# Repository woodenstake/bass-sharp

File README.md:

# New take on Thomas Henry's Bass++ but SMD and possibly a few tweaks

## Simulation in KiCad
I can run transient simulation with ngspice in KiCad for some parts of the design. For instance I can successfully simulate over the trigger circuit and look at the current through of the trigger LED:

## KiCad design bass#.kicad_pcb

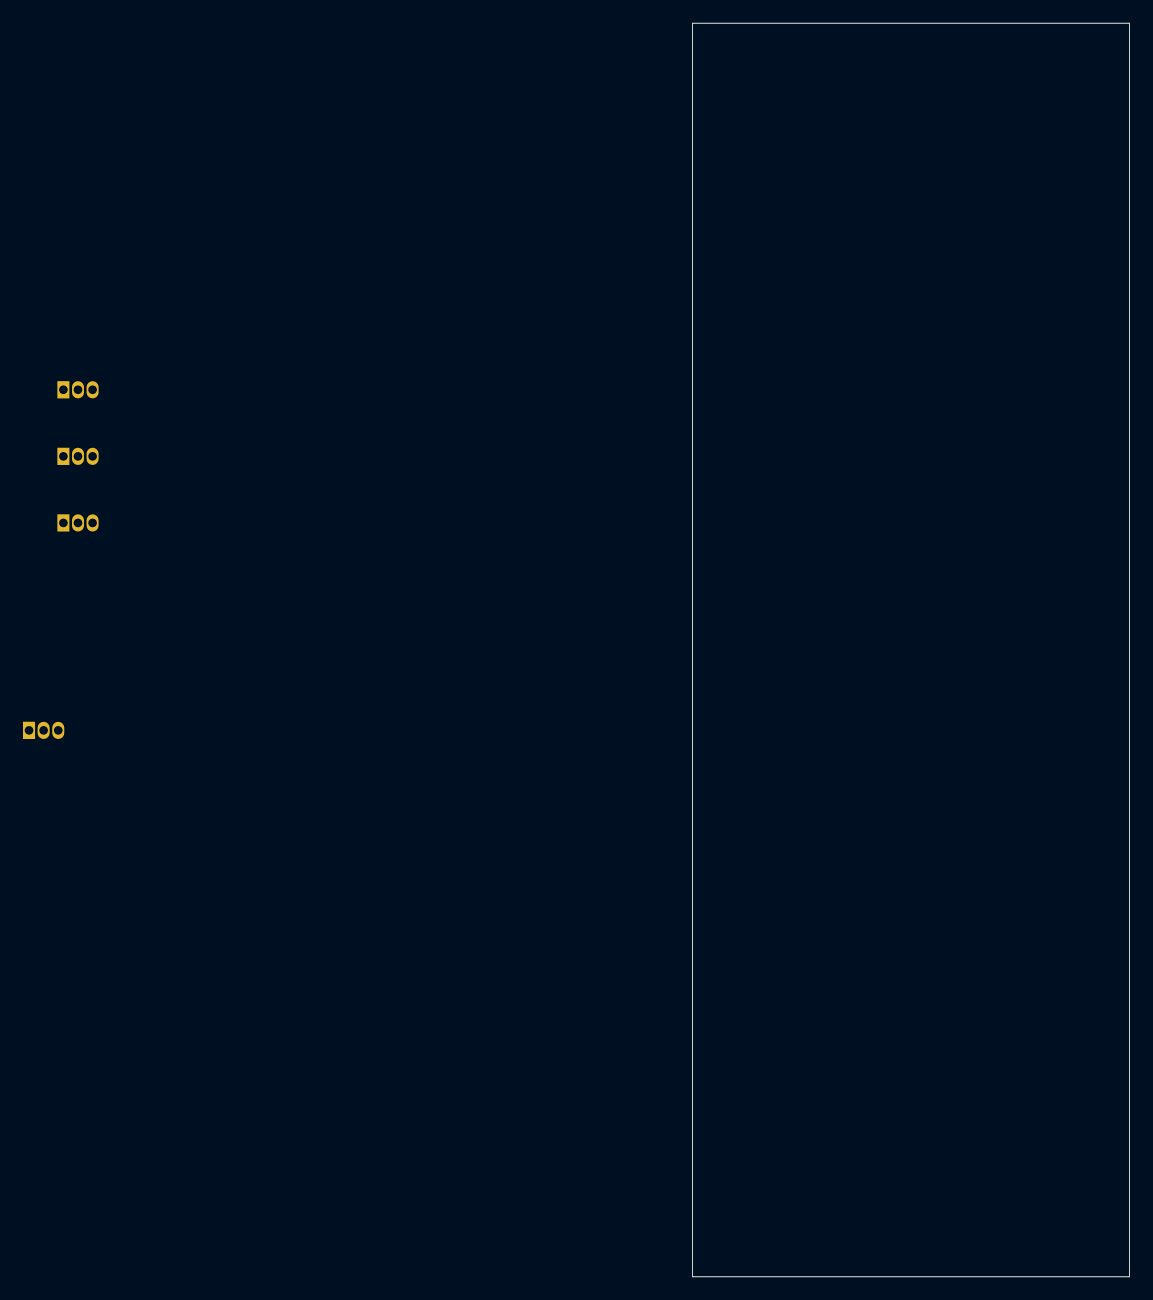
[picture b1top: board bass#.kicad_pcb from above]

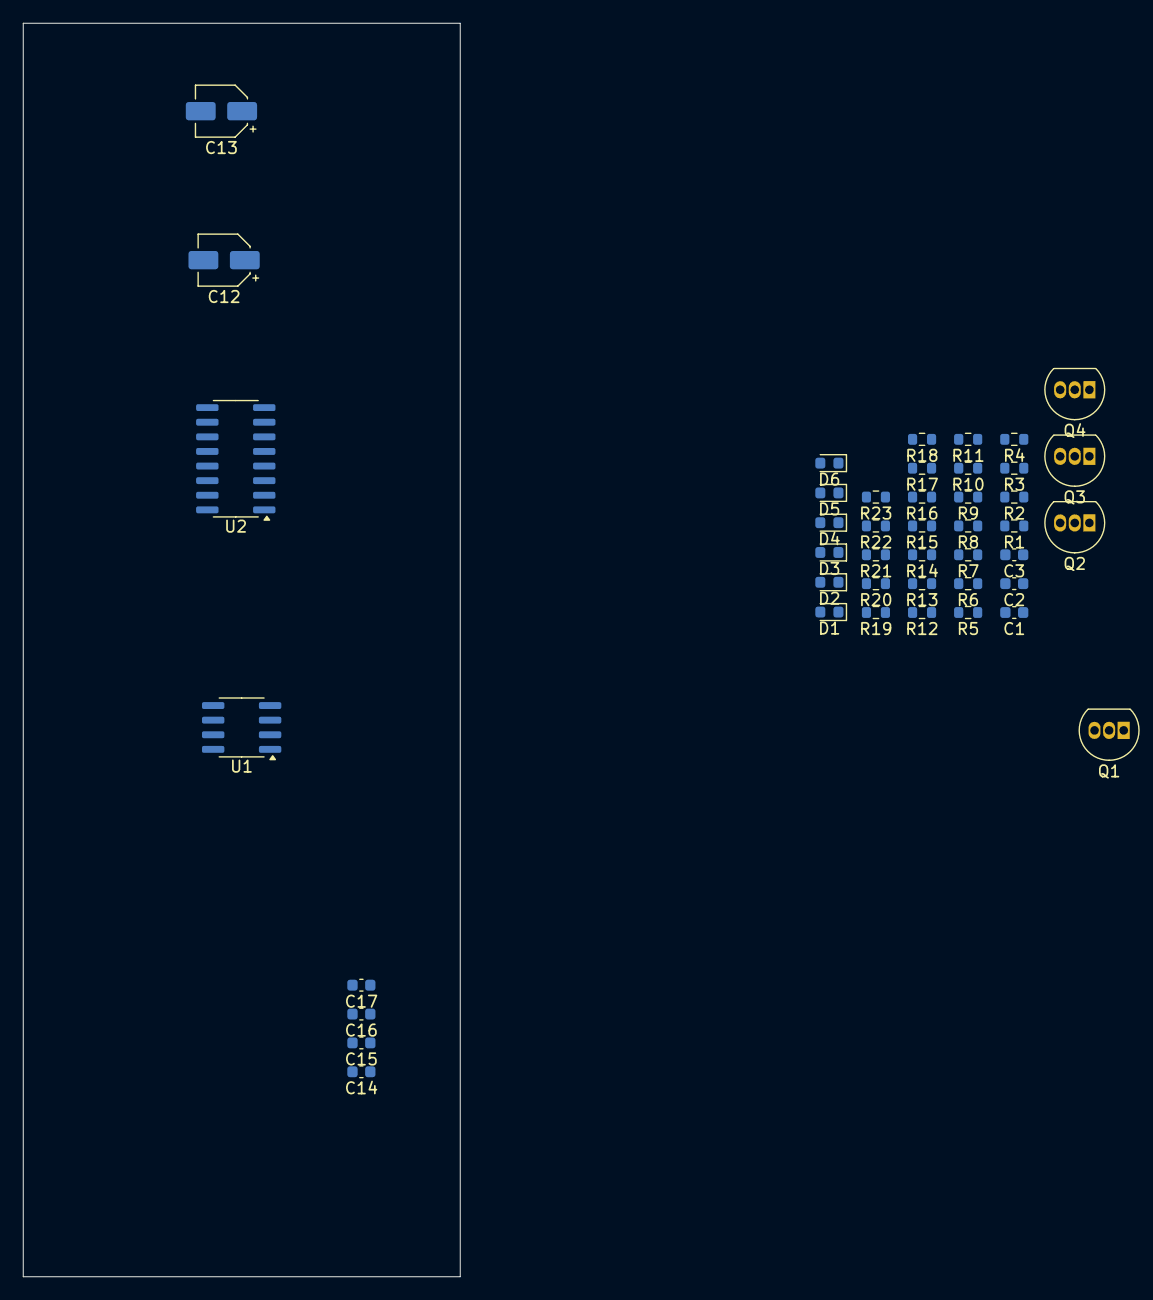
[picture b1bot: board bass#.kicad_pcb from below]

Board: 2 copper layers, 38.0 x 109.0 mm, 44 parts (44 on the bottom side), 27 nets, no tracks yet.

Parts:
C1, C14, C15, C16, C17: 100nF; C_0603_1608Metric
C2: 1nF; C_0603_1608Metric
C3: 10nF; C_0603_1608Metric
C12, C13: 10uF; CP_Elec_4x3
D1, D2, D4, D5, D6: 1N4148; D_0603_1608Metric
D3: LED; LED_0603_1608Metric
Q1, Q2: 2N3904; TO-92_Inline
Q3, Q4: 2N3906; TO-92_Inline
R1, R23: 10k; R_0603_1608Metric
R2: 1M; R_0603_1608Metric
R3: 220k; R_0603_1608Metric
R4, R18: 20K; R_0603_1608Metric
R5, R16: 2K; R_0603_1608Metric
R6: 1K; R_0603_1608Metric
R7, R8, R12, R13, R21: 100K; R_0603_1608Metric
R9: 10K; R_0603_1608Metric
R10: 56K; R_0603_1608Metric
R11: 3.3K; R_0603_1608Metric
R14: 27K; R_0603_1608Metric
R15: 20k; R_0603_1608Metric
R17, R22: 220; R_0603_1608Metric
R19: 5.1K; R_0603_1608Metric
R20: 56k; R_0603_1608Metric
U1: TL072; SOIC-8_3.9x4.9mm_P1.27mm
U2: LM13700; SOIC-16_3.9x9.9mm_P1.27mm

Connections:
0: C1.1, C3.2, C12.2, C13.1, C14.2, C15.1, C16.2, C17.1, D5.1 (K), D6.2 (A), Q1.1 (E), Q3.2 (B), Q4.2 (B), R2.1, R5.1, R11.1, R16.2, R17.2, R20.2, R22.2, U1.5 (+)
+12V: C12.1, C14.1, C16.1, D3.2 (A), Q2.3 (C), R4.2, U1.8 (V+), U2.11 (V+)
-12V: C13.2, C15.2, C17.2, R19.2, R23.2, U1.4 (V-), U2.6 (V-)
unnamed: C1.2, R1.2
unnamed: R12.2, U1.7
unnamed: U2.5, U2.7
unnamed: R18.1, R19.1, U2.8
unnamed: R20.1, U2.10, U2.12
unnamed: R23.1, U2.9
unnamed: C3.1, D1.1 (K), R3.1
unnamed: D2.1 (K), R1.1
unnamed: D3.1 (K), Q1.3 (C)
unnamed: D4.1 (K), R6.2, R9.2
unnamed: D5.2 (A), D6.1 (K), U2.3 (+)
unnamed: Q1.2 (B), R3.2
unnamed: Q2.2 (B), R9.1
unnamed: Q2.1 (E), R15.2
unnamed: Q3.3 (C), U2.16
unnamed: Q3.1 (E), R15.1
unnamed: Q4.3 (C), U2.1
unnamed: Q4.1 (E), R10.1, R13.1, R14.2
unnamed: C2.2, R2.2, U1.3 (+)
unnamed: R7.2, R8.2, R12.1, U1.6 (-)
unnamed: R21.1, R22.1, U2.14 (+)
unnamed: R17.1, U2.13 (-)
unnamed: R16.1, R18.2, U2.4 (-)
TRIG: D1.2 (A), D2.2 (A), D4.2 (A), U1.1

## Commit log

2025-02-03 trying ngspice
2025-02-04 trying simulation
2025-03-30 trying to get simulation to work
2025-04-05 updated to kicad 9
2025-04-05 success in simulating the full circuit!
2025-04-17 work on air
